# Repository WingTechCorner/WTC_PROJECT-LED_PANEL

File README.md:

# LED-PANEL

A small LED panel. Designed with KiCad and files generated and placed into `MANUFACTURING` for production via [JLCPCB](http://www.jlcpcb.com/).

* 0603 white led with LSCS part numbers in the CSV and schematic files.
* 0603 150-ohm resistors ( limits current to around 15-20ma when powered at 3v3 )
* 3 x strips of 16 LED/RESISTOR pairs, in two groups.
* Common GND
* 2 x 3v3 groupings
* headers at head and tail of board to allow for chaining.
* 3V3 and GND paths run along front and back.

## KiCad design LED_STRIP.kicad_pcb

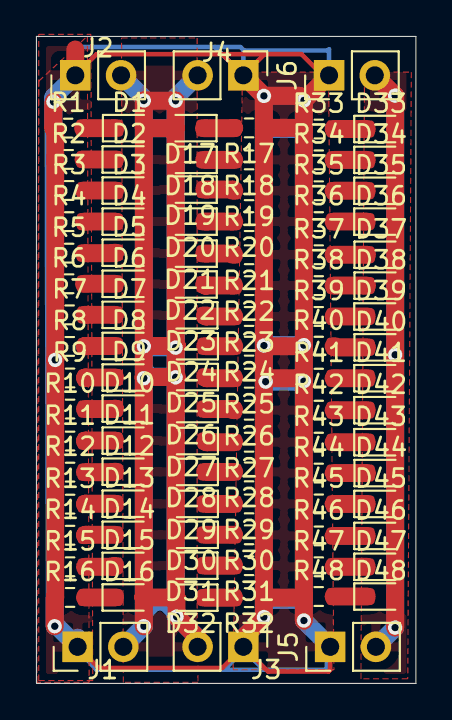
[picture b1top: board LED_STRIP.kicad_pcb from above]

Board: 2 copper layers, 21.1 x 35.9 mm, 102 parts (0 on the bottom side), 50 nets.

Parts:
D1, D2, D3, D4, D5, D6, D7, D8, D9, D10, D11, D12, D13, D14, D15, D16, D17, D18, D19, D20, D21, D22, D23, D24, D25, D26, D27, D28, D29, D30, D31, D32, D33, D34, D35, D36, D37, D38, D39, D40, D41, D42, D43, D44, D45, D46, D47, D48: WHITE_LED; D_0603_1608Metric
J1, J2, J3, J4, J5, J6: Conn_01x02_Male; PinHeader_1x02_P2.54mm_Vertical
R1, R2, R3, R4, R5, R6, R7, R8, R9, R10, R11, R12, R13, R14, R15, R16, R17, R18, R19, R20, R21, R22, R23, R24, R25, R26, R27, R28, R29, R30, R31, R32, R33, R34, R35, R36, R37, R38, R39, R40, R41, R42, R43, R44, R45, R46, R47, R48: 150Ohms-±1%-1_10W-0603; R_0603_1608Metric

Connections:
3V3: D1.2, D2.2, D3.2, D4.2, D5.2, D6.2, D7.2, D8.2, D9.2, D10.2, D11.2, D12.2, D13.2, D14.2, D15.2, D16.2, D17.2, D18.2, D19.2, D20.2, D21.2, D22.2, D23.2, D24.2, D25.2, D26.2, D27.2, D28.2, D29.2, D30.2, D31.2, D32.2, D33.2, D34.2, D35.2, D36.2, D37.2, D38.2, D39.2, D40.2, D41.2, D42.2, D43.2, D44.2, D45.2, D46.2, D47.2, D48.2, J1.2, J2.2, J3.2, J4.2, J5.2, J6.2
GND: J1.1, J2.1, J3.1, J4.1, J5.1, J6.1, R1.1, R2.1, R3.1, R4.1, R5.1, R6.1, R7.1, R8.1, R9.1, R10.1, R11.1, R12.1, R13.1, R14.1, R15.1, R16.1, R17.1, R18.1, R19.1, R20.1, R21.1, R22.1, R23.1, R24.1, R25.1, R26.1, R27.1, R28.1, R29.1, R30.1, R31.1, R32.1, R33.1, R34.1, R35.1, R36.1, R37.1, R38.1, R39.1, R40.1, R41.1, R42.1, R43.1, R44.1, R45.1, R46.1, R47.1, R48.1
unnamed: D1.1, R1.2
unnamed: D2.1, R2.2
unnamed: D3.1, R3.2
unnamed: D4.1, R4.2
unnamed: D5.1, R5.2
unnamed: D6.1, R6.2
unnamed: D7.1, R7.2
unnamed: D8.1, R8.2
unnamed: D9.1, R9.2
unnamed: D10.1, R10.2
unnamed: D11.1, R11.2
unnamed: D12.1, R12.2
unnamed: D13.1, R13.2
unnamed: D14.1, R14.2
unnamed: D15.1, R15.2
unnamed: D16.1, R16.2
unnamed: D17.1, R17.2
unnamed: D18.1, R18.2
unnamed: D19.1, R19.2
unnamed: D20.1, R20.2
unnamed: D21.1, R21.2
unnamed: D22.1, R22.2
unnamed: D23.1, R23.2
unnamed: D24.1, R24.2
unnamed: D25.1, R25.2
unnamed: D26.1, R26.2
unnamed: D27.1, R27.2
unnamed: D28.1, R28.2
unnamed: D29.1, R29.2
unnamed: D30.1, R30.2
unnamed: D31.1, R31.2
unnamed: D32.1, R32.2
unnamed: D33.1, R33.2
unnamed: D34.1, R34.2
unnamed: D35.1, R35.2
unnamed: D36.1, R36.2
unnamed: D37.1, R37.2
unnamed: D38.1, R38.2
unnamed: D39.1, R39.2
unnamed: D40.1, R40.2
unnamed: D41.1, R41.2
unnamed: D42.1, R42.2
unnamed: D43.1, R43.2
unnamed: D44.1, R44.2
unnamed: D45.1, R45.2
unnamed: D46.1, R46.2
unnamed: D47.1, R47.2
unnamed: D48.1, R48.2

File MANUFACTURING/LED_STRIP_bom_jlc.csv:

"Comment","Designator","Footprint","LCSC Part #"
"WHITE_LED","D1,D2,D3,D4,D7,D8,D5,D6,D9,D10,D11,D12,D15,D16,D13,D14,D17,D18,D19,D20,D29,D30,D23,D24,D25,D26,D27,D28,D21,D22,D31,D32,D33,D34,D35,D36,D45,D46,D39,D40,D41,D42,D43,D44,D37,D38,D47,D48","D_0603_1608Metric","C2290"
"150Ohms-±1%-1_10W-0603","R1,R2,R3,R4,R7,R8,R5,R6,R9,R10,R11,R12,R15,R16,R13,R14,R17,R18,R19,R20,R29,R30,R23,R24,R25,R26,R27,R28,R21,R22,R31,R32,R33,R34,R35,R36,R45,R46,R39,R40,R41,R42,R43,R44,R37,R38,R47,R48","R_0603_1608Metric","C22808"

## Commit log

2020-11-08 Adding updates to README.md to provide more information. Adding generated manufacturing files for JLCPCB service provider, inclugin BOM and pick&place/CPL file. Also included KiCad project, schematic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
2020-11-08 Updated description about the 3v3 channels. 2 instead of 3

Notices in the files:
LED_STRIP.kicad_pcb:
(C)2020 Wing Tang Wong
